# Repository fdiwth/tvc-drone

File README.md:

# About

<div align="center">
	
</div>

The TVC(Thrust Vector Control) drone project is a demonstration of the control capabilities that can be achieved in amateur rocketry. Similar to an actual rocket with a TVC system, the drone is capable of balancing and angling itself at desired a desired set-point by vectoring the thrust it produces appropriately. This repository contains the documentation of the project along with sources of both hardware and software that was developed in the duration of the project.

# Navigating the Repository

The repository is mainly split into five sections:

 - tvc-drone/apps
 - tvc-drone/docs
 - tvc-drone/gcs-firmware
 - tvc-drone/drone-firmware
 - tvc-drone/resources

The best way to navigate this repository if you are looking for an in depth guide is to follow along the documentation available in your language of choice below tvc-drone/docs. The documentation explains the design choices, and the links to appropriate sections of the repository.

If you are looking to look at a specific part of the sources, navigating to the appropriately named folders will help find the resources you need.

To get a short overview of the features used in the project, check out the overview section available at tvc-drone/docs/{language}.

# Videos

Click on the images of videos to watch them. Watch video 5 or 6 if you want to see the result.

<div align="center">

</div>

# Disclaimer

This repository is merely a demonstration of what is achievable with a custom-built coaxial TVC drone stack, and is not a step-by-step guide on building one. Despite the project materials being open sourced, it is discouraged to use them directly in one's own project. However, anyone is welcome to use the documentations and source materials as a reference. But treat this as a reference point, not a direct dependency. 

# Contact

Anyone with any questions regarding this project are welcome to reach out through contact informations listed below.

instagram: fd.iwth
email: fdiwth@gmail.com

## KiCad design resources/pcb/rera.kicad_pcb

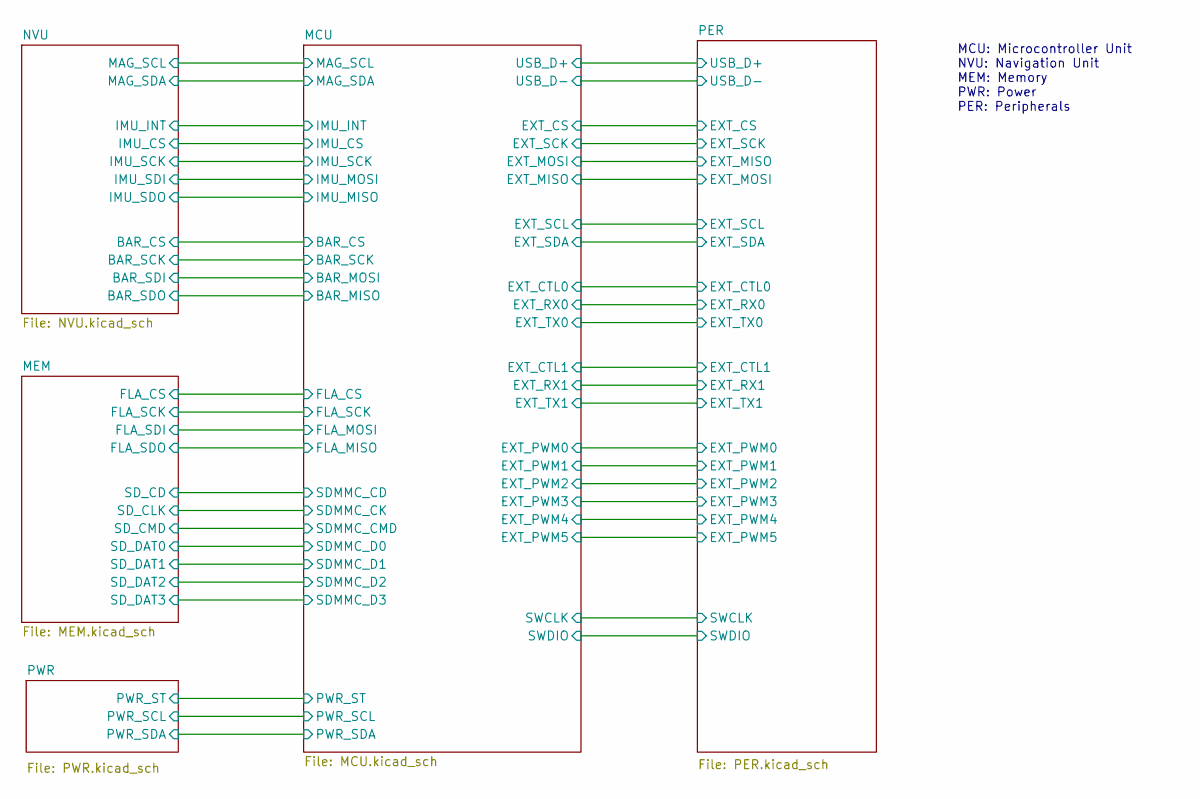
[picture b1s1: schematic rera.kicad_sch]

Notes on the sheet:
MCU: Microcontroller Unit NVU: Navigation Unit MEM: Memory PWR: Power PER: Peripherals

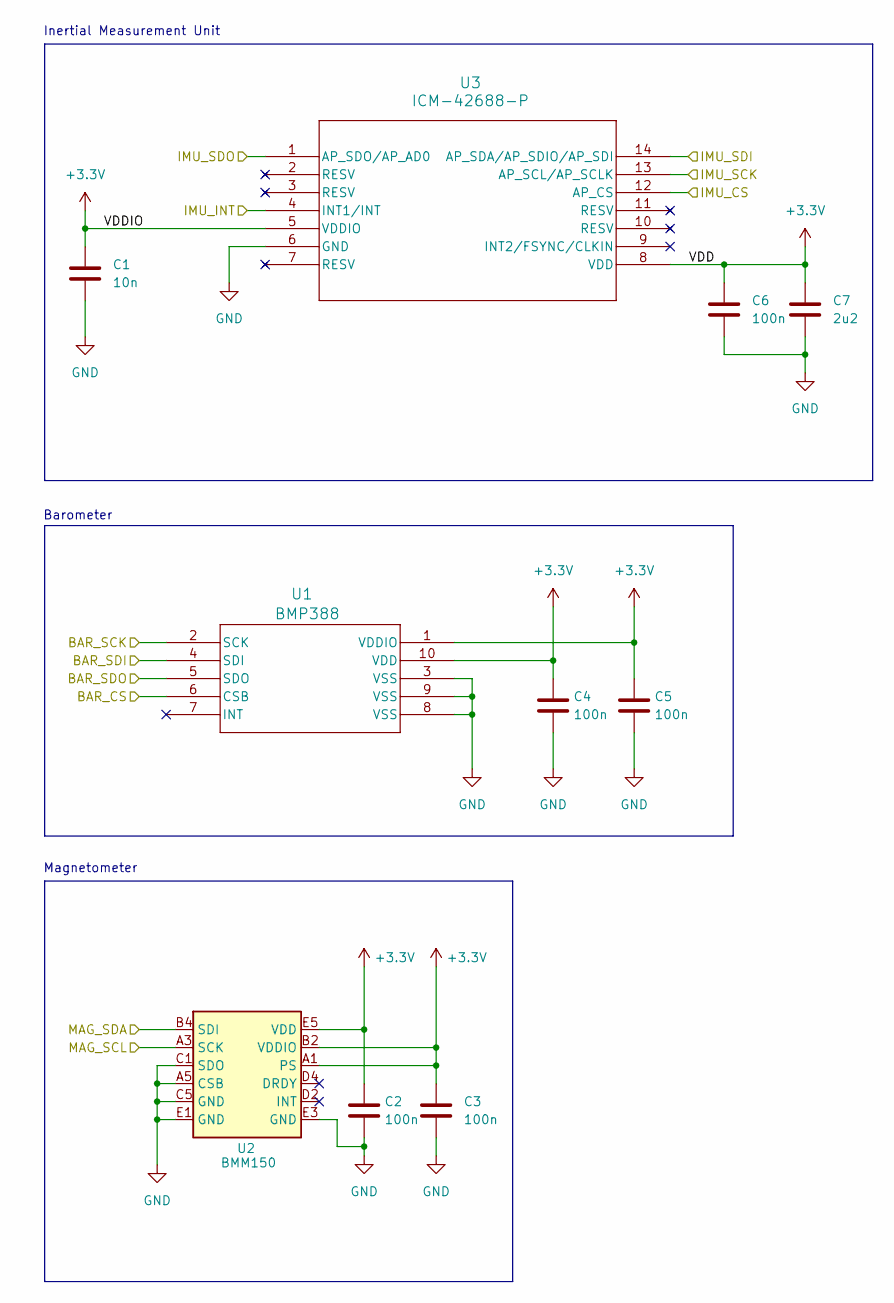
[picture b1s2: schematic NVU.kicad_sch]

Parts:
C1: 10n; C_0402_1005Metric
C2, C3, C4, C5, C6: 100n; C_0402_1005Metric
C7: 2u2; C_0603_1608Metric
U1: BMP388; QFN_BMP388_BOS
U2: BMM150; WLCSP-12_1.56x1.56mm_P0.4mm
U3: ICM-42688-P; LGA14_2P5X3X0P91_TDK

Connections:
+3.3V: C1.1, C2.1, C3.1, C4.1, C5.1, C6.1, C7.1, U1.1 (VDDIO), U1.10 (VDD), U2.A1 (PS), U2.B2 (VDDIO), U2.E5 (VDD), U3.5 (VDDIO), U3.8 (VDD); also elsewhere on the board
/MCU/BAR_MOSI: U1.4 (SDI); also elsewhere on the board
/MCU/BAR_SCK: U1.2 (SCK); also elsewhere on the board
/MCU/EXT_MOSI: U3.14 (AP_SDA/AP_SDIO/AP_SDI); also elsewhere on the board
/MCU/EXT_SCK: U3.13 (AP_SCL/AP_SCLK); also elsewhere on the board
/MCU/GPIO_EXTI6: U3.4 (INT1/INT); also elsewhere on the board
/MCU/I2C1_SCL: U2.A3 (SCK); also elsewhere on the board
/MCU/I2C1_SDA: U2.B4 (SDI); also elsewhere on the board
/MCU/SPI1_CS1: U1.6 (CSB); also elsewhere on the board
/MCU/SPI1_MISO: U1.5 (SDO); also elsewhere on the board
/MCU/SPI2_CS1: U3.12 (AP_CS); also elsewhere on the board
/MCU/SPI2_MISO: U3.1 (AP_SDO/AP_AD0); also elsewhere on the board
GND: C1.2, C2.2, C3.2, C4.2, C5.2, C6.2, C7.2, U1.3 (VSS), U1.8 (VSS), U1.9 (VSS), U2.A5 (CSB), U2.C1 (SDO), U2.C5 (GND), U2.E1 (GND), U2.E3 (GND), U3.6 (GND); also elsewhere on the board

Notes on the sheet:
Inertial Measurement Unit
Magnetometer
Barometer

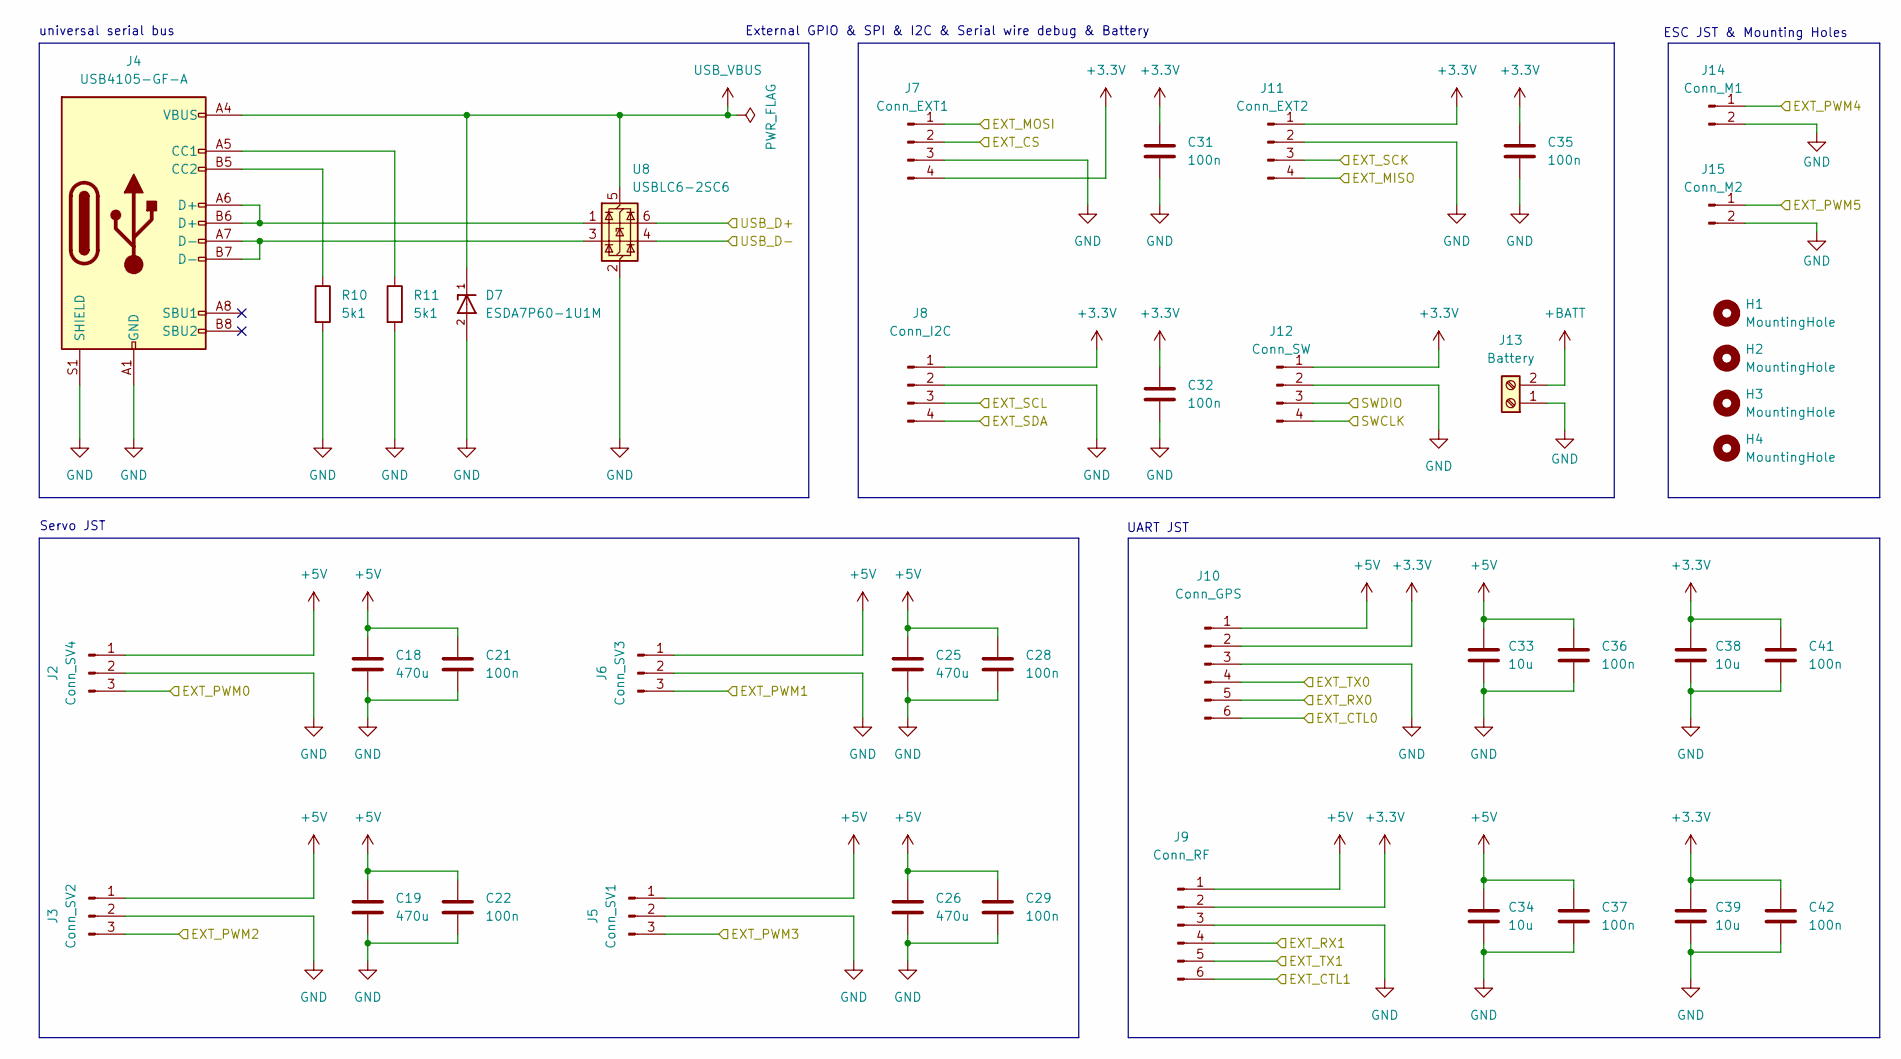
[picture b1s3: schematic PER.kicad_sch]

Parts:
C18, C19, C25, C26: 470u; C_Elec_6.3x7.7
C21, C22, C28, C29, C31, C32, C35, C36, C37, C41, C42: 100n; C_0402_1005Metric
C33, C34, C38, C39: 10u; C_0805_2012Metric
D7: ESDA7P60-1U1M; TVS_ESDA7P60-1U1M; PARTREV 4
H1, H2, H3, H4: MountingHole; MountingHole_3.2mm_M3
J2: Conn_SV4; JST_PH_B3B-PH-K_1x03_P2.00mm_Vertical
J3: Conn_SV2; JST_PH_B3B-PH-K_1x03_P2.00mm_Vertical
J4: USB4105-GF-A; USB_C_Receptacle_GCT_USB4105-xx-A_16P_TopMnt_Horizontal
J5: Conn_SV1; JST_PH_B3B-PH-K_1x03_P2.00mm_Vertical
J6: Conn_SV3; JST_PH_B3B-PH-K_1x03_P2.00mm_Vertical
J7: Conn_EXT1; JST_PH_B4B-PH-K_1x04_P2.00mm_Vertical
J8: Conn_I2C; JST_PH_B4B-PH-K_1x04_P2.00mm_Vertical
J9: Conn_RF; JST_PH_B6B-PH-K_1x06_P2.00mm_Vertical
J10: Conn_GPS; JST_PH_B6B-PH-K_1x06_P2.00mm_Vertical
J11: Conn_EXT2; JST_PH_B4B-PH-K_1x04_P2.00mm_Vertical
J12: Conn_SW; PinHeader_1x04_P2.54mm_Vertical
J13: Battery; TerminalBlock_Phoenix_MKDS-1,5-2-5.08_1x02_P5.08mm_Horizont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
J14: Conn_M1; JST_PH_B2B-PH-K_1x02_P2.00mm_Vertical
J15: Conn_M2; JST_PH_B2B-PH-K_1x02_P2.00mm_Vertical
R10, R11: 5k1; R_0402_1005Metric
U8: USBLC6-2SC6; SOT-23-6

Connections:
+3.3V: C31.1, C32.1, C35.1, C38.1, C39.1, C41.1, C42.1, J7.4, J8.1, J9.2, J10.2, J11.1, J12.1; also elsewhere on the board
+5V: C18.1, C19.1, C21.1, C22.1, C25.1, C26.1, C28.1, C29.1, C33.1, C34.1, C36.1, C37.1, J2.1, J3.1, J5.1, J6.1, J9.1, J10.1; also elsewhere on the board
+BATT: J13.2; also elsewhere on the board
/MCU/EXT_MOSI: J11.4; also elsewhere on the board
/MCU/EXT_SCK: J11.3; also elsewhere on the board
/MCU/GPIO_PA15: J9.6; also elsewhere on the board
/MCU/GPIO_PB3: J10.6; also elsewhere on the board
/MCU/I2C1_SCL: J8.3; also elsewhere on the board
/MCU/I2C1_SDA: J8.4; also elsewhere on the board
/MCU/SPI2_CS2: J7.2; also elsewhere on the board
/MCU/SPI2_MISO: J7.1; also elsewhere on the board
/MCU/SWCLK: J12.4; also elsewhere on the board
/MCU/SWDIO: J12.3; also elsewhere on the board
/MCU/TIM2_CH1: J14.1; also elsewhere on the board
/MCU/TIM2_CH2: J15.1; also elsewhere on the board
/MCU/TIM3_CH1: J2.3; also elsewhere on the board
/MCU/TIM3_CH2: J6.3; also elsewhere on the board
/MCU/TIM3_CH3: J3.3; also elsewhere on the board
/MCU/TIM3_CH4: J5.3; also elsewhere on the board
/MCU/UART2_RX: J10.4; also elsewhere on the board
/MCU/UART2_TX: J10.5; also elsewhere on the board
/MCU/UART3_RX: J9.5; also elsewhere on the board
/MCU/UART3_TX: J9.4; also elsewhere on the board
/MCU/USB_OTG_FS_D+: U8.6 (I/O1); also elsewhere on the board
/MCU/USB_OTG_FS_D-: U8.4 (I/O2); also elsewhere on the board
GND: C18.2, C19.2, C21.2, C22.2, C25.2, C26.2, C28.2, C29.2, C31.2, C32.2, C33.2, C34.2, C35.2, C36.2, C37.2, C38.2, C39.2, C41.2, C42.2, D7.2, J2.2, J3.2, J4.A1 (GND), J4.A12 (GND), J4.B1 (GND), J4.B12 (GND), J4.S1 (SHIELD), J5.2, J6.2, J7.3, J8.2, J9.3, J10.3, J11.2, J12.2, J13.1, J14.2, J15.2, R10.2, R11.2, U8.2 (GND); also elsewhere on the board
unnamed: J4.A5 (CC1), R11.1
unnamed: J4.B5 (CC2), R10.1
unnamed: J4.A6 (D+), J4.B6 (D+), U8.1 (I/O1)
unnamed: J4.A7 (D-), J4.B7 (D-), U8.3 (I/O2)
USB_VBUS: D7.1, J4.A4 (VBUS), J4.A9 (VBUS), J4.B4 (VBUS), J4.B9 (VBUS), U8.5 (VBUS); also elsewhere on the board

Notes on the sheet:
External GPIO & SPI & I2C & Serial wire debug & Battery
UART JST
Servo JST
ESC JST & Mounting Holes
universal serial bus

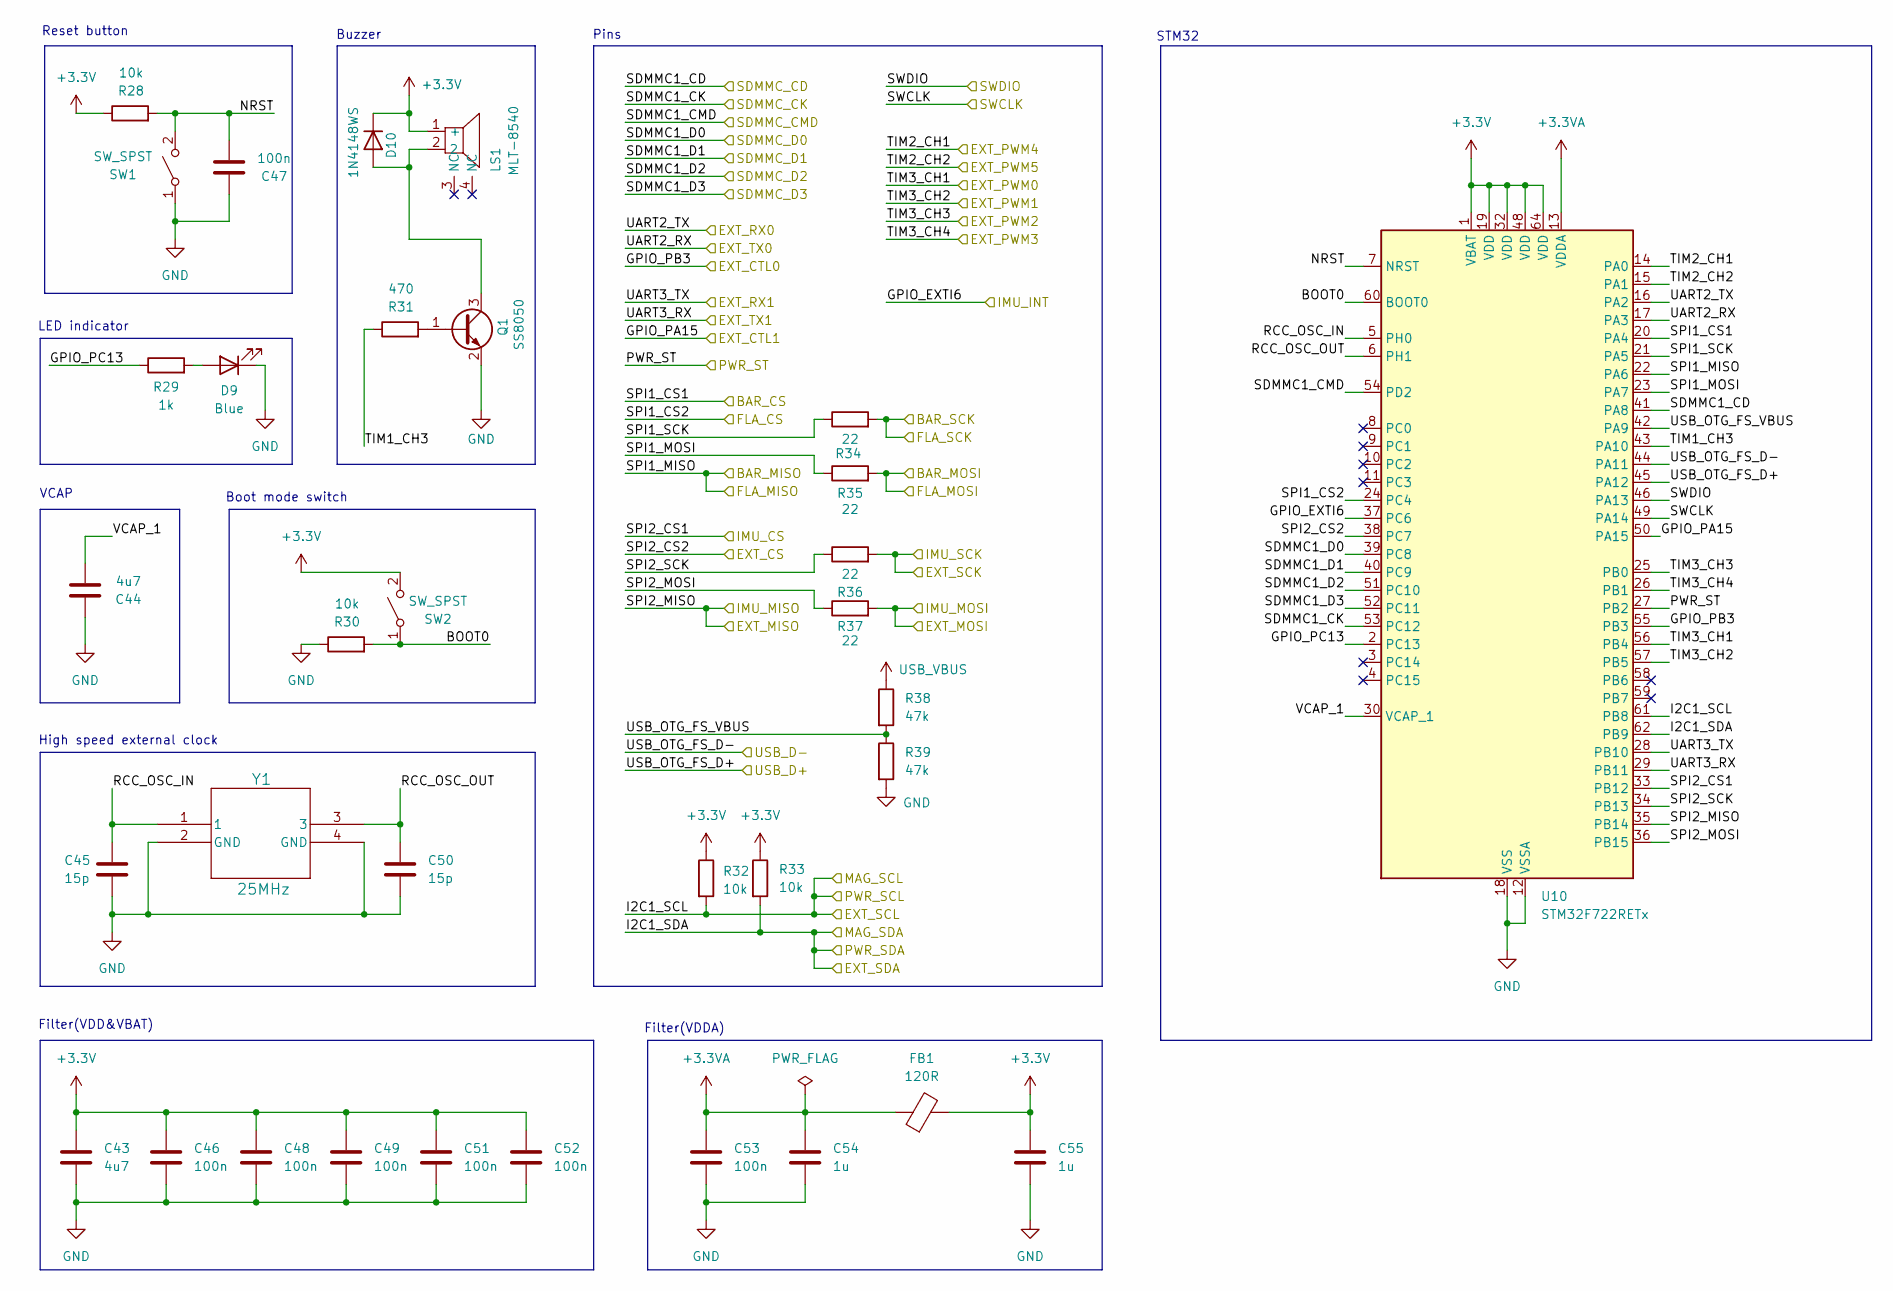
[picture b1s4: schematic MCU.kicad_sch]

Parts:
C43, C44: 4u7; C_0603_1608Metric
C45, C50: 15p; C_0402_1005Metric
C46, C47, C48, C49, C51, C52, C53: 100n; C_0402_1005Metric
C54, C55: 1u; C_0603_1608Metric
D9: Blue; LED_0603_1608Metric
D10: 1N4148WS; D_SOD-323
FB1: 120R; L_0603_1608Metric
LS1: MLT-8540; MPN MLT-8540; LCSC Part C95300
Q1: SS8050; SOT-23
R28, R30, R32, R33: 10k; R_0402_1005Metric
R29: 1k; R_0402_1005Metric
R31: 470; R_0603_1608Metric
R34, R35, R36, R37: 22; R_0603_1608Metric
R38, R39: 47k; R_0402_1005Metric
SW1, SW2: SW_SPST; SW_SPST_TS-1088-xR020
U10: STM32F722RETx; LQFP-64_10x10mm_P0.5mm
Y1: 25MHz; SMT_MOB4SI_YXC

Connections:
+3.3V: C43.1, C46.1, C48.1, C49.1, C51.1, C52.1, C55.1, D10.1 (K), FB1.2, LS1.1 (+), R28.1, R32.1, R33.1, SW2.2 (B), U10.1 (VBAT), U10.19 (VDD), U10.32 (VDD), U10.48 (VDD), U10.64 (VDD); also elsewhere on the board
+3.3VA: C53.1, C54.1, FB1.1, U10.13 (VDDA)
/MCU/BAR_MOSI: R35.2; also elsewhere on the board
/MCU/BAR_SCK: R34.2; also elsewhere on the board
/MCU/BOOT0: R30.2, SW2.1 (A), U10.60 (BOOT0)
/MCU/EXT_MOSI: R37.2; also elsewhere on the board
/MCU/EXT_SCK: R36.2; also elsewhere on the board
/MCU/GPIO_EXTI6: U10.37 (PC6); also elsewhere on the board
/MCU/GPIO_PA15: U10.50 (PA15); also elsewhere on the board
/MCU/GPIO_PB3: U10.55 (PB3); also elsewhere on the board
/MCU/GPIO_PC13: R29.1, U10.2 (PC13)
/MCU/I2C1_SCL: R32.2, U10.61 (PB8); also elsewhere on the board
/MCU/I2C1_SDA: R33.2, U10.62 (PB9); also elsewhere on the board
/MCU/NRST: C47.2, R28.2, SW1.2 (B), U10.7 (NRST)
/MCU/PWR_ST: U10.27 (PB2); also elsewhere on the board
/MCU/RCC_OSC_IN: C45.1, U10.5 (PH0), Y1.1
/MCU/RCC_OSC_OUT: C50.1, U10.6 (PH1), Y1.3
/MCU/SDMMC1_CD: U10.41 (PA8); also elsewhere on the board
/MCU/SDMMC1_CK: U10.53 (PC12); also elsewhere on the board
/MCU/SDMMC1_CMD: U10.54 (PD2); also elsewhere on the board
/MCU/SDMMC1_D0: U10.39 (PC8); also elsewhere on the board
/MCU/SDMMC1_D1: U10.40 (PC9); also elsewhere on the board
/MCU/SDMMC1_D2: U10.51 (PC10); also elsewhere on the board
/MCU/SDMMC1_D3: U10.52 (PC11); also elsewhere on the board
/MCU/SPI1_CS1: U10.20 (PA4); also elsewhere on the board
/MCU/SPI1_CS2: U10.24 (PC4); also elsewhere on the board
/MCU/SPI1_MISO: U10.22 (PA6); also elsewhere on the board
/MCU/SPI1_MOSI: R35.1, U10.23 (PA7)
/MCU/SPI1_SCK: R34.1, U10.21 (PA5)
/MCU/SPI2_CS1: U10.33 (PB12); also elsewhere on the board
/MCU/SPI2_CS2: U10.38 (PC7); also elsewhere on the board
/MCU/SPI2_MISO: U10.35 (PB14); also elsewhere on the board
/MCU/SPI2_MOSI: R37.1, U10.36 (PB15)
/MCU/SPI2_SCK: R36.1, U10.34 (PB13)
/MCU/SWCLK: U10.49 (PA14); also elsewhere on the board
/MCU/SWDIO: U10.46 (PA13); also elsewhere on the board
/MCU/TIM1_CH3: R31.1, U10.43 (PA10)
/MCU/TIM2_CH1: U10.14 (PA0); also elsewhere on the board
/MCU/TIM2_CH2: U10.15 (PA1); also elsewhere on the board
/MCU/TIM3_CH1: U10.56 (PB4); also elsewhere on the board
/MCU/TIM3_CH2: U10.57 (PB5); also elsewhere on the board
/MCU/TIM3_CH3: U10.25 (PB0); also elsewhere on the board
/MCU/TIM3_CH4: U10.26 (PB1); also elsewhere on the board
/MCU/UART2_RX: U10.17 (PA3); also elsewhere on the board
/MCU/UART2_TX: U10.16 (PA2); also elsewhere on the board
/MCU/UART3_RX: U10.29 (PB11); also elsewhere on the board
/MCU/UART3_TX: U10.28 (PB10); also elsewhere on the board
/MCU/USB_OTG_FS_D+: U10.45 (PA12); also elsewhere on the board
/MCU/USB_OTG_FS_D-: U10.44 (PA11); also elsewhere on the board
/MCU/USB_OTG_FS_VBUS: R38.2, R39.1, U10.42 (PA9)
/MCU/VCAP_1: C44.2, U10.30 (VCAP_1)
GND: C43.2, C44.1, C45.2, C46.2, C47.1, C48.2, C49.2, C50.2, C51.2, C52.2, C53.2, C54.2, C55.2, D9.1 (K), Q1.2 (E), R30.1, R39.2, SW1.1 (A), U10.12 (VSSA), U10.18 (VSS), U10.31 (VSS), U10.47 (VSS), U10.63 (VSS), Y1.2 (GND), Y1.4 (GND); also elsewhere on the board
unnamed: D9.2 (A), R29.2
unnamed: D10.2 (A), LS1.2, Q1.3 (C)
unnamed: Q1.1 (B), R31.2
USB_VBUS: R38.1; also elsewhere on the board

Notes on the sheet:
Pins
High speed external clock
STM32
Buzzer
Boot mode switch
Filter(VDDA)
Reset button
Filter(VDD&VBAT)
LED indicator
VCAP

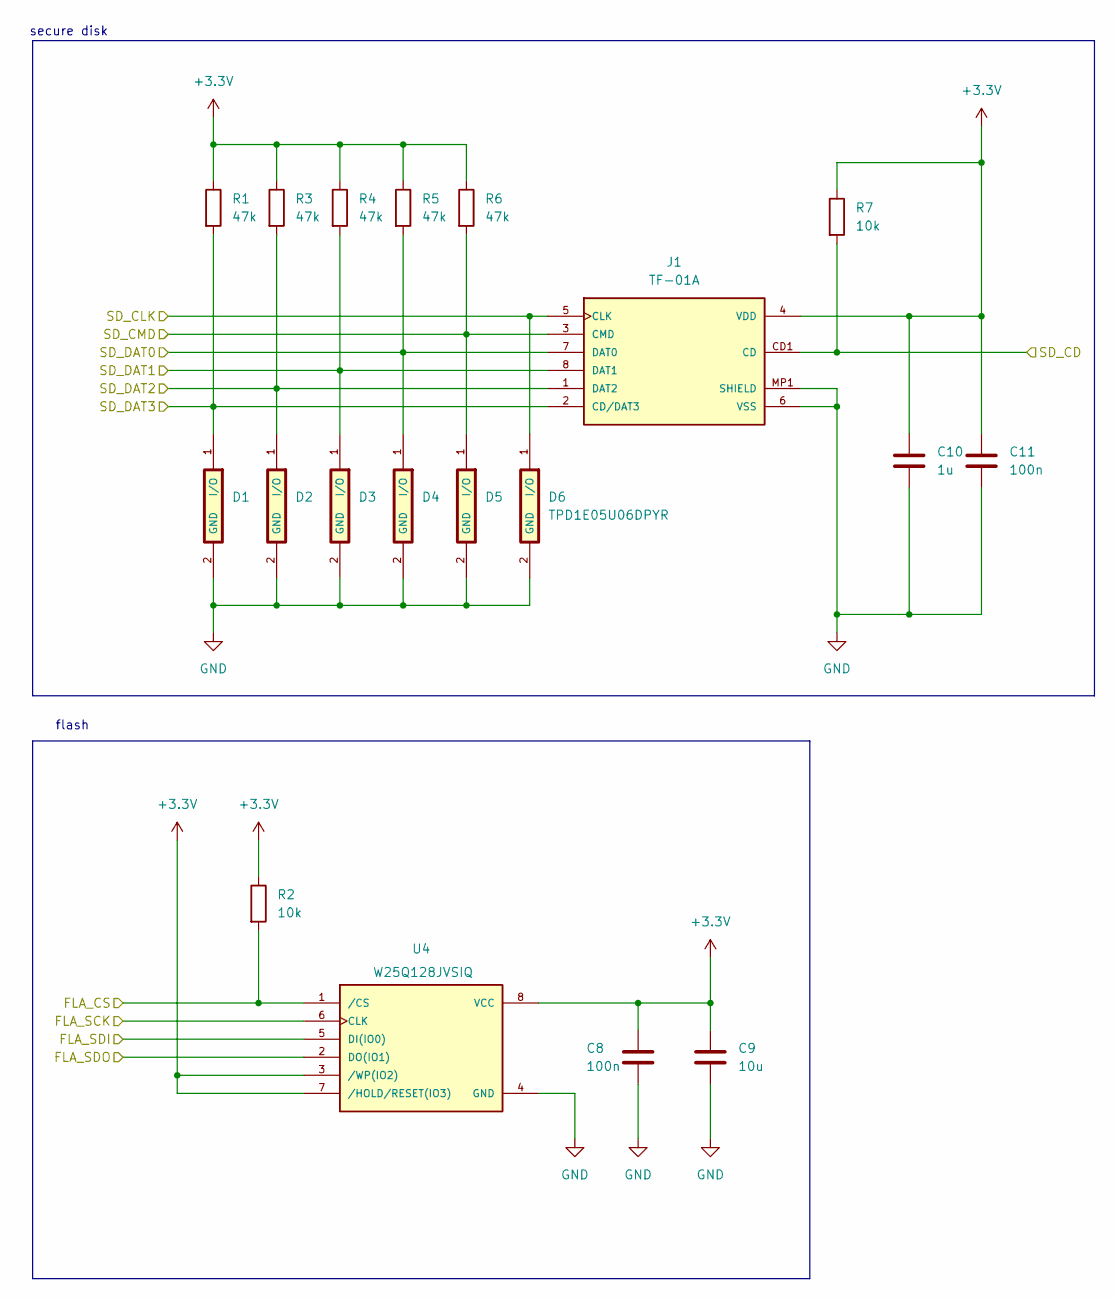
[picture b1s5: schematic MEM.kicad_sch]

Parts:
C8, C11: 100n; C_0402_1005Metric
C9: 10u; C_0805_2012Metric
C10: 1u; C_0603_1608Metric
D1, D2, D3, D4, D5, D6: TPD1E05U06DPYR; DIO_TPD1E05U06DPYR
J1: TF-01A
R1, R3, R4, R5, R6: 47k; R_0402_1005Metric
R2, R7: 10k; R_0402_1005Metric
U4: W25Q128JVSIQ; SOIC127P790X216-8N; PARTREV I

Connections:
+3.3V: C8.1, C9.1, C10.1, C11.1, J1.4 (VDD), R1.1, R2.1, R3.1, R4.1, R5.1, R6.1, R7.1, U4.3 (/WP(IO2)), U4.7 (/HOLD/RESET(IO3)), U4.8 (VCC); also elsewhere on the board
/MCU/BAR_MOSI: U4.5 (DI(IO0)); also elsewhere on the board
/MCU/BAR_SCK: U4.6 (CLK); also elsewhere on the board
/MCU/SDMMC1_CD: J1.CD1 (CD), R7.2; also elsewhere on the board
/MCU/SDMMC1_CK: D6.1 (I/O), J1.5 (CLK); also elsewhere on the board
/MCU/SDMMC1_CMD: D5.1 (I/O), J1.3 (CMD), R6.2; also elsewhere on the board
/MCU/SDMMC1_D0: D4.1 (I/O), J1.7 (DAT0), R5.2; also elsewhere on the board
/MCU/SDMMC1_D1: D3.1 (I/O), J1.8 (DAT1), R4.2; also elsewhere on the board
/MCU/SDMMC1_D2: D2.1 (I/O), J1.1 (DAT2), R3.2; also elsewhere on the board
/MCU/SDMMC1_D3: D1.1 (I/O), J1.2 (CD/DAT3), R1.2; also elsewhere on the board
/MCU/SPI1_CS2: R2.2, U4.1 (/CS); also elsewhere on the board
/MCU/SPI1_MISO: U4.2 (DO(IO1)); also elsewhere on the board
GND: C8.2, C9.2, C10.2, C11.2, D1.2 (GND), D2.2 (GND), D3.2 (GND), D4.2 (GND), D5.2 (GND), D6.2 (GND), J1.6 (VSS), J1.MP1 (SHIELD), J1.MP2 (SHIELD), J1.MP3 (SHIELD), J1.MP4 (SHIELD), U4.4 (GND); also elsewhere on the board

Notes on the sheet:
secure disk
flash

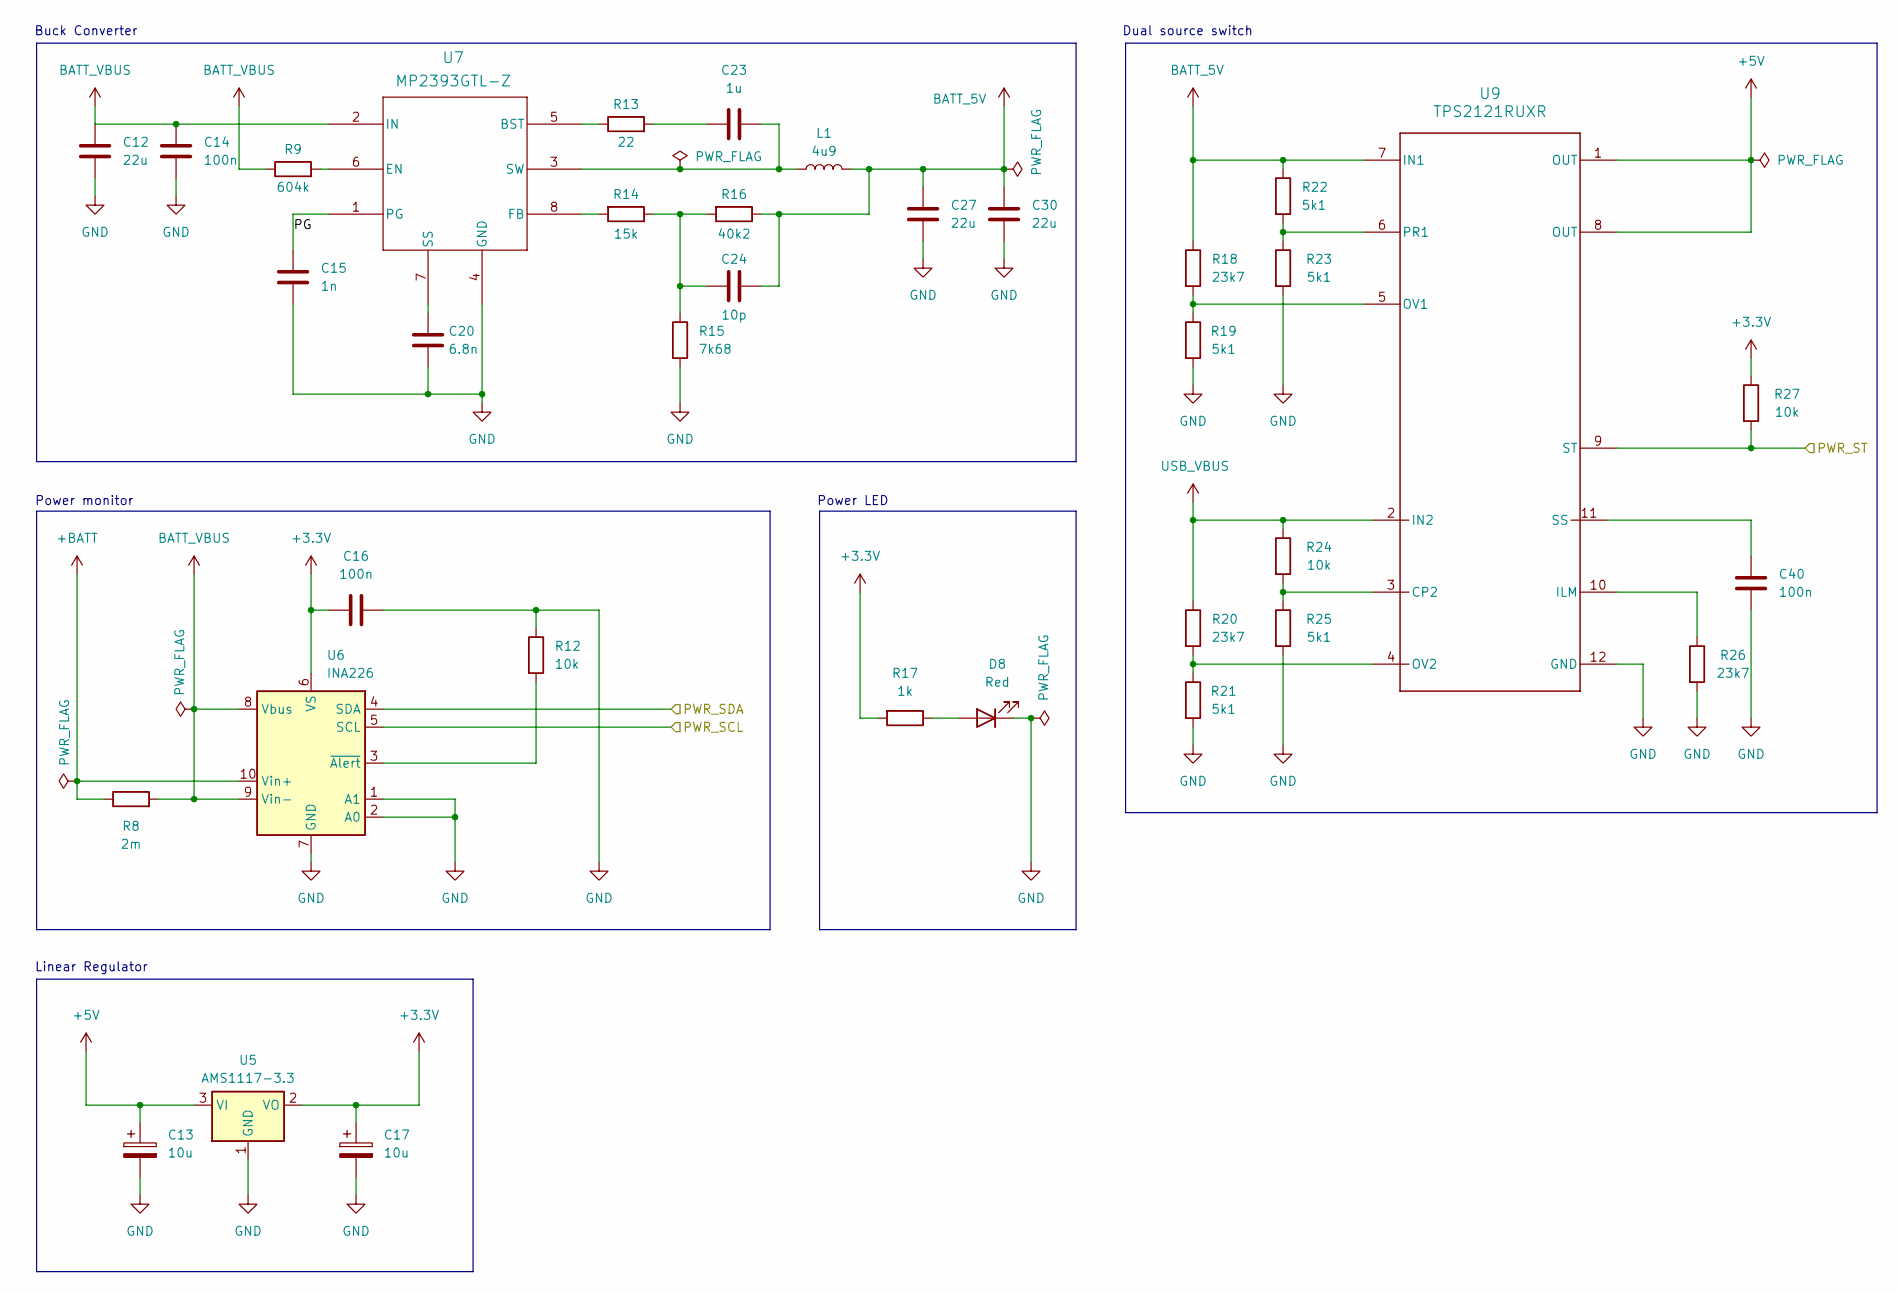
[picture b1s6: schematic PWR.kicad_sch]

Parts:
C12, C27, C30: 22u; C_0805_2012Metric
C13, C17: 10u; CP_EIA-3216-18_Kemet-A
C14, C16, C40: 100n; C_0402_1005Metric
C15: 1n; C_0402_1005Metric
C20: 6.8n; C_0603_1608Metric
C23: 1u; C_0603_1608Metric
C24: 10p; C_0402_1005Metric
D8: Red; LED_0603_1608Metric
L1: 4u9; HSB-0650-4R9-M
R8: 2m; R_1206_3216Metric
R9: 604k; R_0402_1005Metric
R12, R24, R27: 10k; R_0402_1005Metric
R13: 22; R_0603_1608Metric
R14: 15k; R_0603_1608Metric
R15: 7k68; R_0603_1608Metric
R16: 40k2; R_0603_1608Metric
R17: 1k; R_0402_1005Metric
R18, R20, R26: 23k7; R_0402_1005Metric
R19, R21, R22, R23, R25: 5k1; R_0402_1005Metric
U5: AMS1117-3.3; SOT-223-3_TabPin2
U6: INA226; VSSOP-10_3x3mm_P0.5mm
U7: MP2393GTL-Z; SOT583_MP2393
U9: TPS2121RUXR; RUX0012A

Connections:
+3.3V: C16.1, C17.1, R17.2, R27.1, U5.2 (VO), U6.6 (VS); also elsewhere on the board
+5V: C13.1, U5.3 (VI), U9.1 (OUT), U9.8 (OUT); also elsewhere on the board
+BATT: R8.1, U6.10 (Vin+); also elsewhere on the board
/MCU/I2C1_SCL: U6.5 (SCL); also elsewhere on the board
/MCU/I2C1_SDA: U6.4 (SDA); also elsewhere on the board
/MCU/PWR_ST: R27.2, U9.9 (ST); also elsewhere on the board
/PWR/PG: C15.2, U7.1 (PG)
BATT_5V: C24.1, C27.1, C30.1, L1.2, R16.1, R18.1, R22.1, U9.7 (IN1)
BATT_VBUS: C12.1, C14.1, R8.2, R9.1, U6.8 (Vbus), U6.9 (Vin-), U7.2 (IN)
GND: C12.2, C13.2, C14.2, C15.1, C16.2, C17.2, C20.1, C27.2, C30.2, C40.2, D8.1 (K), R12.1, R15.2, R19.2, R21.2, R23.2, R25.2, R26.2, U5.1 (GND), U6.1 (A1), U6.2 (A0), U6.7 (GND), U7.4 (GND), U9.12 (GND); also elsewhere on the board
unnamed: C23.1, R13.2
unnamed: C24.2, R14.1, R15.1, R16.2
unnamed: D8.2 (A), R17.1
unnamed: R12.2, U6.3 (~Alert)
unnamed: R13.1, U7.5 (BST)
unnamed: R9.2, U7.6 (EN)
unnamed: R14.2, U7.8 (FB)
unnamed: C20.2, U7.7 (SS)
unnamed: C23.2, L1.1, U7.3 (SW)
unnamed: R24.2, R25.1, U9.3 (CP2)
unnamed: R26.1, U9.10 (ILM)
unnamed: R18.2, R19.1, U9.5 (OV1)
unnamed: R20.2, R21.1, U9.4 (OV2)
unnamed: R22.2, R23.1, U9.6 (PR1)
unnamed: C40.1, U9.11 (SS)
USB_VBUS: R20.1, R24.1, U9.2 (IN2); also elsewhere on the board

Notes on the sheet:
Power LED
Power monitor
Linear Regulator
Buck Converter
Dual source switch

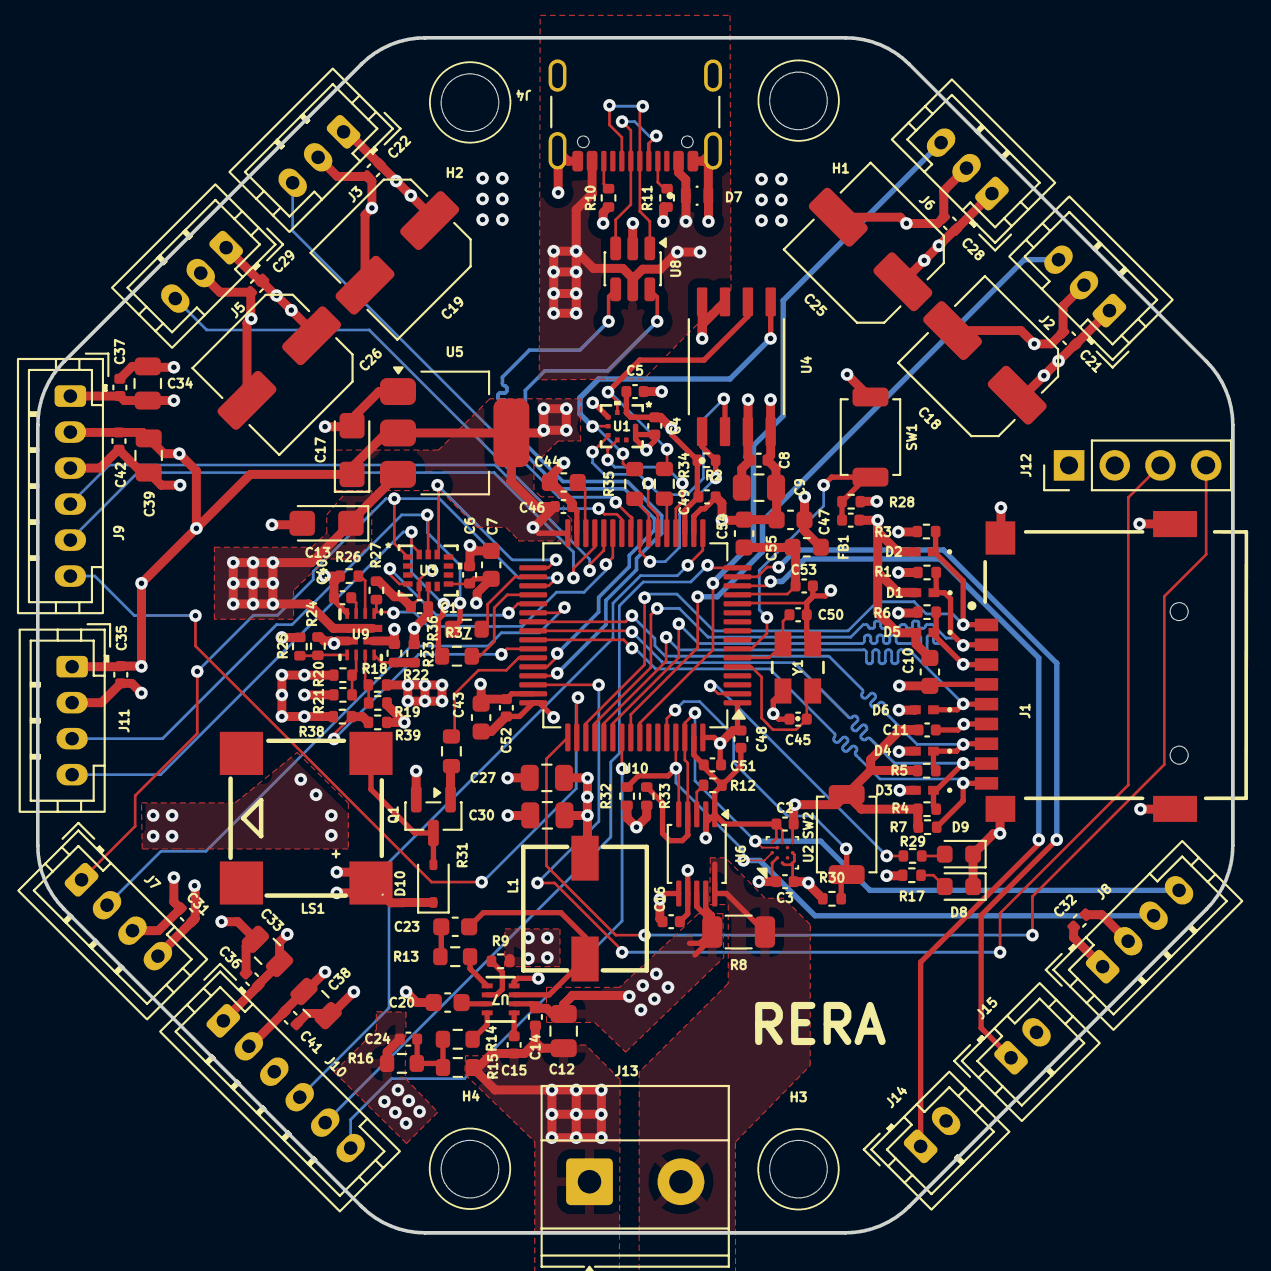
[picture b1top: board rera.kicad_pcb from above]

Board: 4 copper layers, 66.4 x 66.4 mm, 140 parts (0 on the bottom side), 80 nets.

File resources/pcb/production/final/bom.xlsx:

Designator | Footprint | Quantity | Value | JLCPCB#
C1 | 402.0 | 1.0 | 10n | C15195
C10, C23, C54, C55 | 603.0 | 4.0 | 1u | C15849
C11, C14, C16, C2, C21, C22, C28, C29, C3, C31, C32, C35, C36, C37, C4, C40, C4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 | 402.0 | 28.0 | 100n | C45783
C12, C27, C30 | 805.0 | 3.0 | 22u | C7171
C13, C17 | CP_EIA-3216-18_Kemet-A | 2.0 | 10u | C1523
C15 | 402.0 | 1.0 | 1n | C3354
C18, C19, C25, C26 | C_Elec_6.3x7.7 | 4.0 | 470u | C1525
C20 | 603.0 | 1.0 | 6.8n | C1631
C24 | 402.0 | 1.0 | 10p | C32949
C33, C34, C38, C39, C9 | 805.0 | 5.0 | 10u | C19666
C43, C44 | 603.0 | 2.0 | 4u7 | C1548
C45, C50 | 402.0 | 2.0 | 15p | C23630
C7 | 603.0 | 1.0 | 2u2 | C15850
D1, D2, D3, D4, D5, D6 | DIO_TPD1E05U06DPYR | 6.0 | TPD1E05U06DPYR | C436349
D10 | D_SOD-323 | 1.0 | 1N4148WS | C2128
D7 | TVS_ESDA7P60-1U1M | 1.0 | ESDA7P60-1U1M | C1975146
D8 | 603.0 | 1.0 | Red | C2286
D9 | 603.0 | 1.0 | Blue | C2288
FB1 | 603.0 | 1.0 | 120R | C14709
J1 | TF-01A | 1.0 | TF-01A | C91145
J10 | JST_PH_B6B-PH-K_1x06_P2.00mm_Vertical | 1.0 | Conn_GPS | C33478
J11 | JST_PH_B4B-PH-K_1x04_P2.00mm_Vertical | 1.0 | Conn_EXT2 | C2321
J12 | PinHeader_1x04_P2.54mm_Vertical | 1.0 | Conn_SW | C5116483
J13 | TerminalBlock_Phoenix_MKDS-1,5-2-5.08_1x02_P5.08mm_Horizontal | 1.0 | Battery | C89120
J14 | JST_PH_B2B-PH-K_1x02_P2.00mm_Vertical | 1.0 | Conn_M1 | C2319
J15 | JST_PH_B2B-PH-K_1x02_P2.00mm_Vertical | 1.0 | Conn_M2 | C2319
J2 | JST_PH_B3B-PH-K_1x03_P2.00mm_Vertical | 1.0 | Conn_SV4 | C2320
J3 | JST_PH_B3B-PH-K_1x03_P2.00mm_Vertical | 1.0 | Conn_SV2 | C2320
J4 | USB_C_Receptacle_GCT_USB4105-xx-A_16P_TopMnt_Horizontal | 1.0 | USB4105-GF-A | C5184243
J5 | JST_PH_B3B-PH-K_1x03_P2.00mm_Vertical | 1.0 | Conn_SV1 | C2320
J6 | JST_PH_B3B-PH-K_1x03_P2.00mm_Vertical | 1.0 | Conn_SV3 | C2320
J7 | JST_PH_B4B-PH-K_1x04_P2.00mm_Vertical | 1.0 | Conn_EXT1 | C2321
J8 | JST_PH_B4B-PH-K_1x04_P2.00mm_Vertical | 1.0 | Conn_I2C | C2321
J9 | JST_PH_B6B-PH-K_1x06_P2.00mm_Vertical | 1.0 | Conn_RF | C33478
L1 | HSB-0650-4R9-M | 1.0 | 4u9 | C53373573
LS1 | MLT-8540 | 1.0 | MLT-8540 | C95300
Q1 | SOT-23 | 1.0 | SS8050 | C2150
R1, R3, R38, R39, R4, R5, R6 | 402.0 | 7.0 | 47k | C25792
R10, R11, R19, R21, R22, R23, R25 | 402.0 | 7.0 | 5k1 | C25905
R12, R2, R24, R27, R28, R30, R32, R33, R7 | 402.0 | 9.0 | 10k | C1203
R13, R34, R35, R36, R37 | 603.0 | 5.0 | 22.0 | C22809
R14 | 603.0 | 1.0 | 15k | C23102
R15 | 603.0 | 1.0 | 7k68 | C12447
R16 | 603.0 | 1.0 | 40k2 | C11702
R17, R29 | 402.0 | 2.0 | 1k | C226363
R18, R20, R26 | 402.0 | 3.0 | 23k7 | C60489
R31 | 603.0 | 1.0 | 470.0 | C23179
R8 | 1206.0 | 1.0 | 2m | C92124
R9 | 402.0 | 1.0 | 604k | C27013
SW1, SW2 | SW_SPST_TS-1088-xR020 | 2.0 | SW_SPST | C720477
U1 | QFN_BMP388_BOS | 1.0 | BMP388 | C54582187
U10 | LQFP-64_10x10mm_P0.5mm | 1.0 | STM32F722RETx | C118207
U2 | WLCSP-12_1.56x1.56mm_P0.4mm | 1.0 | BMM150 | C171681
U3 | LGA14_2P5X3X0P91_TDK | 1.0 | ICM-42688-P | C54308212
U4 | SOIC127P790X216-8N | 1.0 | W25Q128JVSIQ | C97521
U5 | SOT-223-3_TabPin2 | 1.0 | AMS1117-3.3 | C6186
U6 | VSSOP-10_3x3mm_P0.5mm | 1.0 | INA226 | C49851
U7 | SOT583_MP2393 | 1.0 | MP2393GTL-Z | C6674609
U8 | SOT-23-6 | 1.0 | USBLC6-2SC6 | C7519
U9 | RUX0012A | 1.0 | TPS2121RUXR | C485916
Y1 | SMT_MOB4SI_YXC | 1.0 | 25MHz | C9006
